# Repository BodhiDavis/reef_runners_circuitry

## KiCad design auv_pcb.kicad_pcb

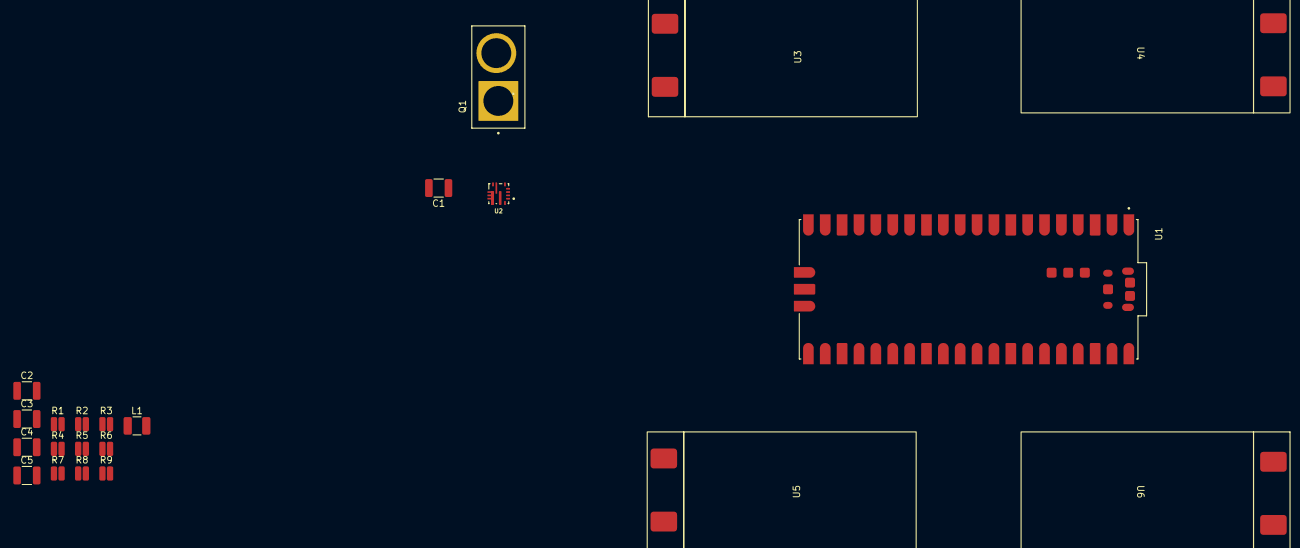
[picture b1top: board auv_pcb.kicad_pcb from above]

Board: 2 copper layers, 22 parts (0 on the bottom side), 14 nets, no tracks yet.

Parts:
C1: 15uF; C_1210_3225Metric
C2: 100nF; C_1210_3225Metric
C3: 100 nF; C_1210_3225Metric
C4: 100 pF; C_1210_3225Metric
C5: 47 uF; C_1210_3225Metric
L1: 3.3 uH; L_1210_3225Metric
Q1: XT60_YELLOW; AMASS_XT60PB-M
R1: 1.669 mOhm; R_0508_1220Metric
R2: 1mOhm; R_0508_1220Metric
R3: 280 mOhm; R_0508_1220Metric
R4: 100 kOhm; R_0508_1220Metric
R5: 17.7 mOhm; R_0508_1220Metric
R6: 20 kOhm; R_0508_1220Metric
R7: 73.2 kOhm; R_0508_1220Metric
R8: 10 kOhm; R_0508_1220Metric
R9: 3.037 mOhm; R_0508_1220Metric
U1: SC0917; MODULE_SC0917
U2: TPS56637RPAR; CONV_TPS56637RPAR
U3, U4, U5, U6: esc

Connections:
/+V: C1.1, C2.1, Q1.1, U2.8 (VIN), U3.1 (+V_in), U4.1 (+V_in), U5.1 (+V_in), U6.1 (+V_in)
/POWER/5V: C5.1, R4.2, R5.2, R6.2, R7.2
/POWER/SW: L1.1, R3.1, U2.6 (SW)
GND: Q1.2, R1.2, R2.2, R8.1, R9.2, U1.3 (GND), U1.8 (GND), U1.13 (GND), U1.18 (GND), U1.23 (GND), U1.28 (GND), U1.38 (GND), U1.D2 (GND), U2.3 (AGND), U2.9 (PGND), U2.10 (MODE), U3.2 (-V_in), U4.2 (-V_in), U5.2 (-V_in), U6.2 (-V_in)
unnamed: C1.2, R1.1
unnamed: C2.2, R2.1
unnamed: C3.1, R3.2
unnamed: C4.1, R6.1
unnamed: C5.2, R9.1
unnamed: L1.2, R5.1
unnamed: C3.2, U2.7 (BOOT)
unnamed: C4.2, R7.1, R8.2, U2.2 (FB)
unnamed: R4.1, U2.4 (PG)
USB_SHIELD: U1.A (USB_SHIELD), U1.B (USB_SHIELD), U1.C (USB_SHIELD), U1.D (USB_SHIELD)

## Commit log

2026-02-15 init
2026-02-16 idek
